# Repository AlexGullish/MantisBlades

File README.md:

# Mantis Blades

A Cyberpunk 2077-inspired wearable cosplay recreation of the Cyberpunk Mantis Blades

## How to Use

- The extension and retraction is controlled by the joystick held in the users hand
- Squeezing the joystick extends the blade to its max
- Releasing retracts it
- The exact extension can be controlled by modulating the joystick

# BoM
| Item | Qty | Supplier | Cost/item | Total Cost | link |
| :--- | :--- | :--- | :--- | :--- | :--- |
| Joystick | 1 | BerryBase | $1.89 | $1.89 | https://www.berrybase.ch/analoges-2-achsen-joystick-modul-mit-select-taster |
| Servo | 2 | BerryBase | $3.11 | $6.22 | https://www.berrybase.ch/sg92r-micro-servo |
| Breadboard | 1 | BerryBase | $2.01 | $2.01 | https://www.berrybase.ch/mini-breadboard-mit-170-kontakten/farbe-weiss |
| Estimated total  |  |  |  | $10.12 |  |

Parts such as the ESP32, wires or printing material will be used but do not require funding

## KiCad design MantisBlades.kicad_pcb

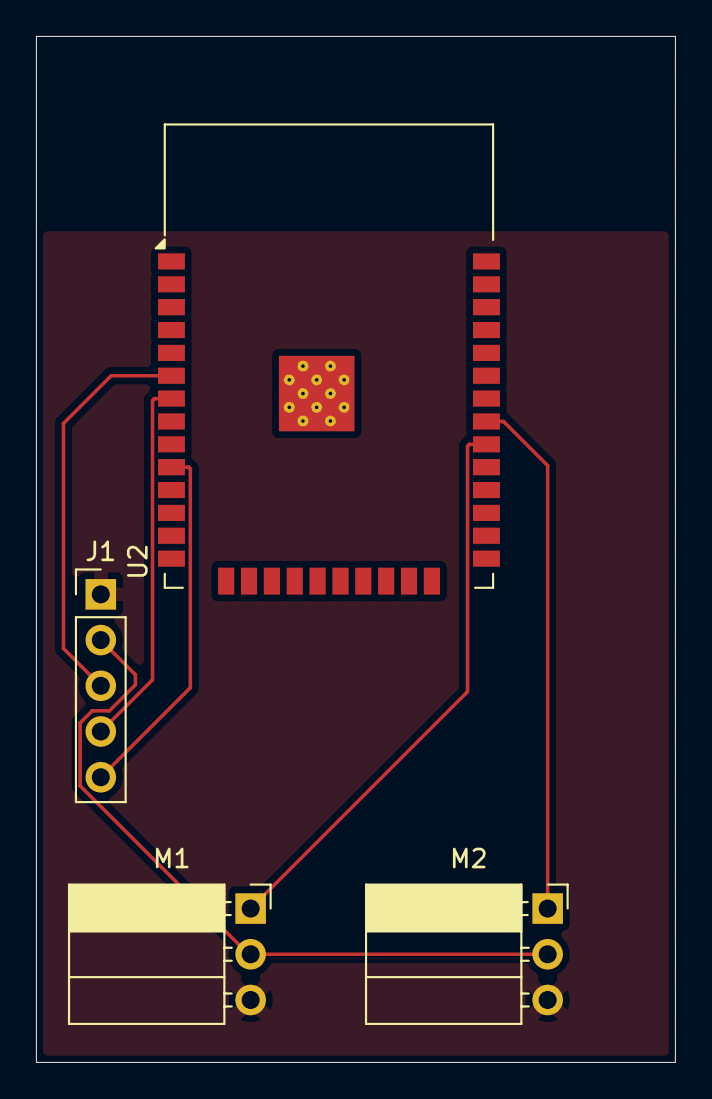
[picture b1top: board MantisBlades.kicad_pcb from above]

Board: 2 copper layers, 35.5 x 57.0 mm, 5 parts (0 on the bottom side), 7 nets.

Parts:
BT1: Battery; Battery_CR1225
J1: Conn_01x05_Pin; PinHeader_1x05_P2.54mm_Vertical
M1, M2: Motor_Servo; PinSocket_1x03_P2.54mm_Horizontal
U2: ESP32-WROOM-32

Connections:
GND: J1.1, M1.3 (-), M2.3 (-)
unnamed: J1.2, M1.2 (+), M2.2 (+)
unnamed: J1.3, U2.6 (IO34)
unnamed: J1.4, U2.7 (IO35)
unnamed: J1.5, U2.10 (IO25)
unnamed: M1.1 (PWM), U2.30 (IO18)
unnamed: M2.1 (PWM), U2.31 (IO19)
